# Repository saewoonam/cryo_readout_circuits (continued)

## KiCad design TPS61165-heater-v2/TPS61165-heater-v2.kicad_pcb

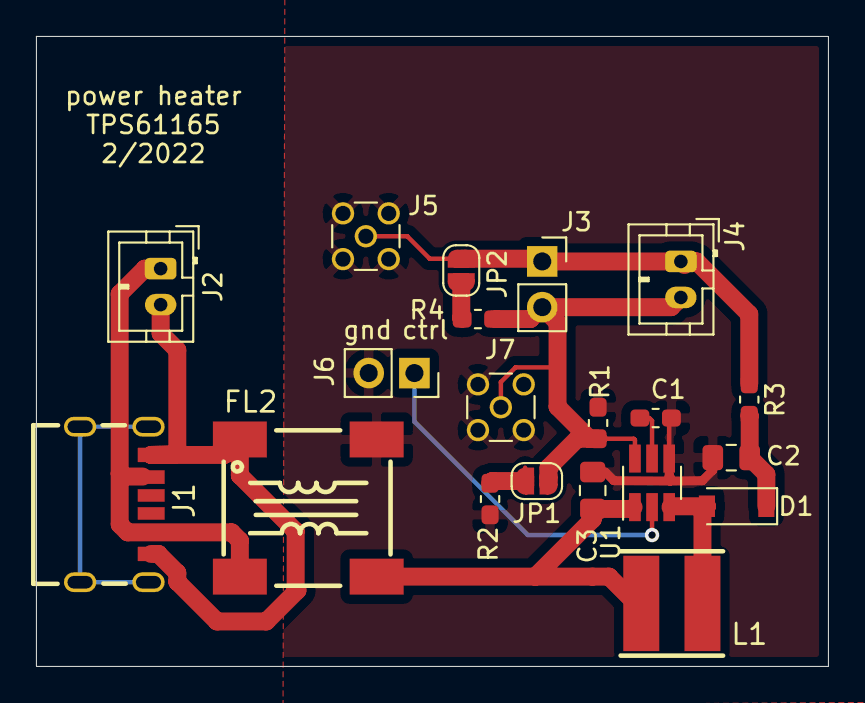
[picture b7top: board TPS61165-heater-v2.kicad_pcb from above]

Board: 2 copper layers, 44.0 x 35.0 mm, 20 parts (0 on the bottom side), 12 nets.

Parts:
C1: 220nF; C_0603_1608Metric_Pad1.05x0.95mm_HandSolder
C2: 1uF_0805_50V; C_0805_2012Metric_Pad1.15x1.40mm_HandSolder
C3: 4.7uF_0805_25V; C_0805_2012Metric_Pad1.15x1.40mm_HandSolder
D1: MBR0540; D_SOD-123
FL2: EMI_Filter_LL_1423_250uH; FILTER-SMD_4P-L8.8-W8.5-TL
J1: USB_C_KoreanHroparts_6P; USB-C-KoreanHroparts
J2, J4: A2001WV-2P; JST_PH_B2B-PH-K_1x02_P2.00mm_Vertical
J3, J6: Conn_01x02_Female; PinSocket_1x02_P2.54mm_Vertical
J5, J7: MMCX; MMCX_JLC
JP1, JP2: Jumper_2_Open; SolderJumper-2_P1.3mm_Open_RoundedPad1.0x1.5mm
L1: 10uH; IND-SMD_L4.7-W4.7
R1, R3: 1; R_0603_1608Metric_Pad1.05x0.95mm_HandSolder
R2, R4: 10; R_0603_1608Metric_Pad1.05x0.95mm_HandSolder
U1: TPS61165; SOT-23-6_Handsoldering

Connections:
+5VD: C3.1, FL2.3, L1.1, U1.1
GND: C1.2, C2.2, C3.2, FL2.4, J5.2, J6.2, J7.2, R1.2, R2.2, U1.4
unnamed: C1.1, U1.5
unnamed: C2.1, D1.1, R3.2
unnamed: D1.2, L1.2, U1.3
unnamed: FL2.1, J1.A12, J1.B12, J2.2
unnamed: FL2.2, J1.A9, J1.B9, J2.1
unnamed: J3.1, J4.1, J5.1, JP2.1, R3.1
unnamed: J3.2, J4.2, J7.1, JP1.1, R1.1, R4.1, U1.6
unnamed: J6.1, U1.2
unnamed: JP1.2, R2.1
unnamed: JP2.2, R4.2

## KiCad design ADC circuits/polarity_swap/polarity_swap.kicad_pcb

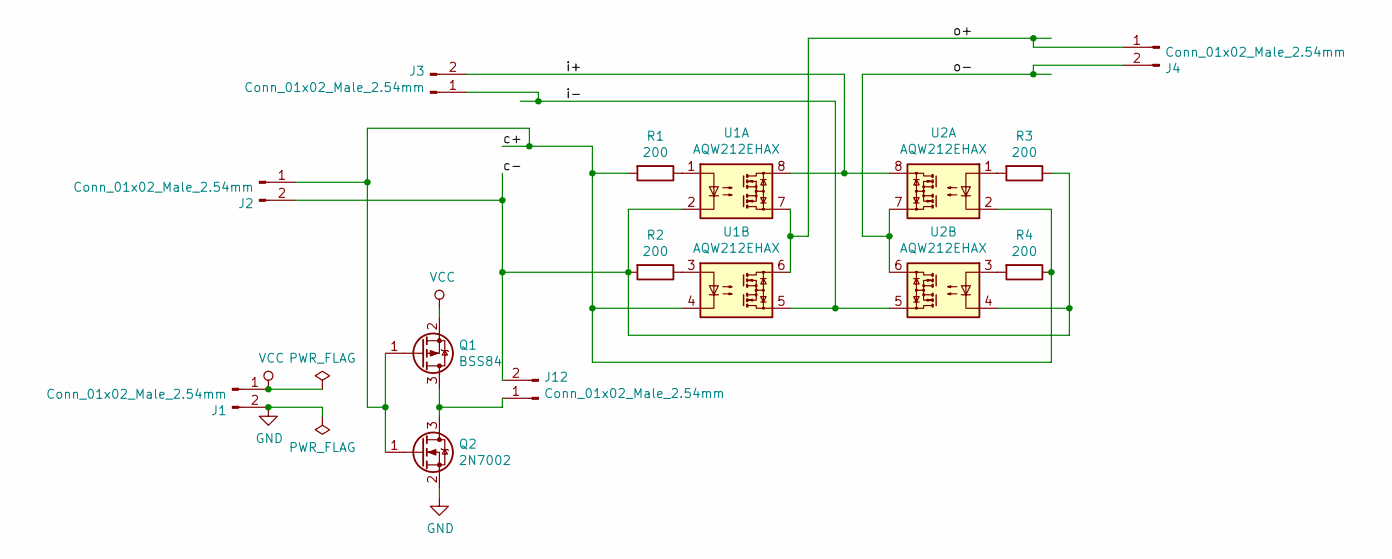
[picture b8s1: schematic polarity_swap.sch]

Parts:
J1, J2, J3, J4, J12: Conn_01x02_Male_2.54mm; PinHeader_1x02_P2.54mm_Vertical; MPN PZ254V-11-02P; LCSC C492401
Q1: BSS84; SOT-23; MPN LBSS84LT1G; LCSC C8492
Q2: 2N7002; SOT-23; MPN 2N7002; LCSC C8545
R1, R2, R3, R4: 200; R_0603_1608Metric_Pad1.05x0.95mm_HandSolder; MPN 0603WAF2000T5E; LCSC C8218
U1, U2: AQW212EHAX; SMD-8_L9.8-W6.4-P2.54-LS10.0-BL; MPN AQW212EHAX; LCSC C161815

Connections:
/c+: J2.1, Q1.1 (G), Q2.1 (G), R1.2, R4.1, U1.4, U2.2
/c-: J2.2, J12.2, R2.2, R3.1, U1.2, U2.4
/i+: J3.2, U1.8, U2.8
/i-: J3.1, U1.5, U2.5
/o+: J4.1, U1.6, U1.7
/o-: J4.2, U2.6, U2.7
GND: J1.2, Q2.2 (S)
unnamed: J12.1, Q1.3 (D), Q2.3 (D)
unnamed: R1.1, U1.1
unnamed: R2.1, U1.3
unnamed: R3.2, U2.1
unnamed: R4.2, U2.3
VCC: J1.1, Q1.2 (S)

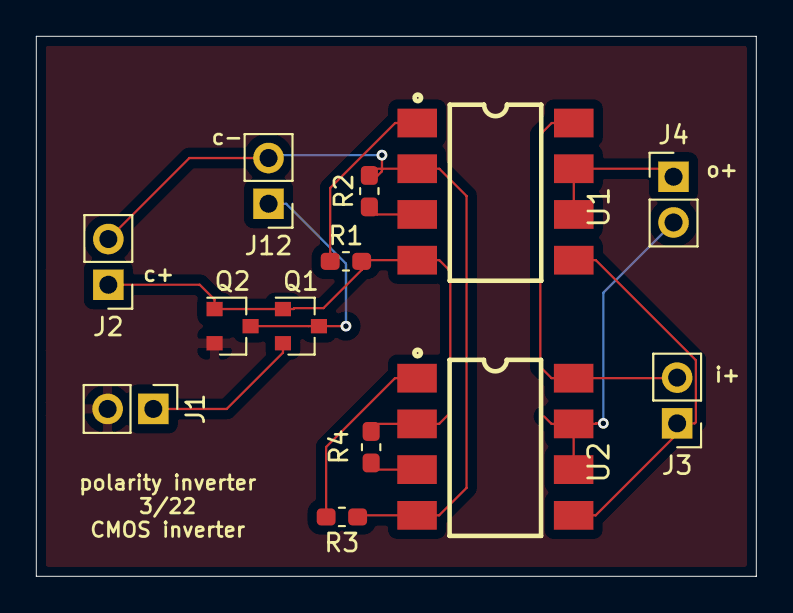
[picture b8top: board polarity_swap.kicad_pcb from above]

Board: 2 copper layers, 40.0 x 30.0 mm, 13 parts (0 on the bottom side), 13 nets.

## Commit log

2021-11-19 Add 2ch ADS112C04
2022-03-31 Update github
2022-03-31 Update gitignore
2022-04-01 Update design
2022-04-01 Add 47ohms for compatibility with ADS122U04.
2022-06-01 Add power-two-wre and tweaks to sq_lockin_v3
2022-06-03 add uart mux versions
2022-07-15 Add TPS61165-heater-v5
2022-07-19 add sq_lockin_v4
2022-08-26 add low power heater
